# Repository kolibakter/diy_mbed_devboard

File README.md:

# DIY mbed devboard.

This board is for prototyping the mbed HDK for LPC1768 on a board.

[`Link to BOM`](https://docs.google.com/spreadsheets/d/1FSUZfUqJZ9Wz-e41FTdCeESnldcWK53uHcWxY3N1jUs/edit?usp=sharing)

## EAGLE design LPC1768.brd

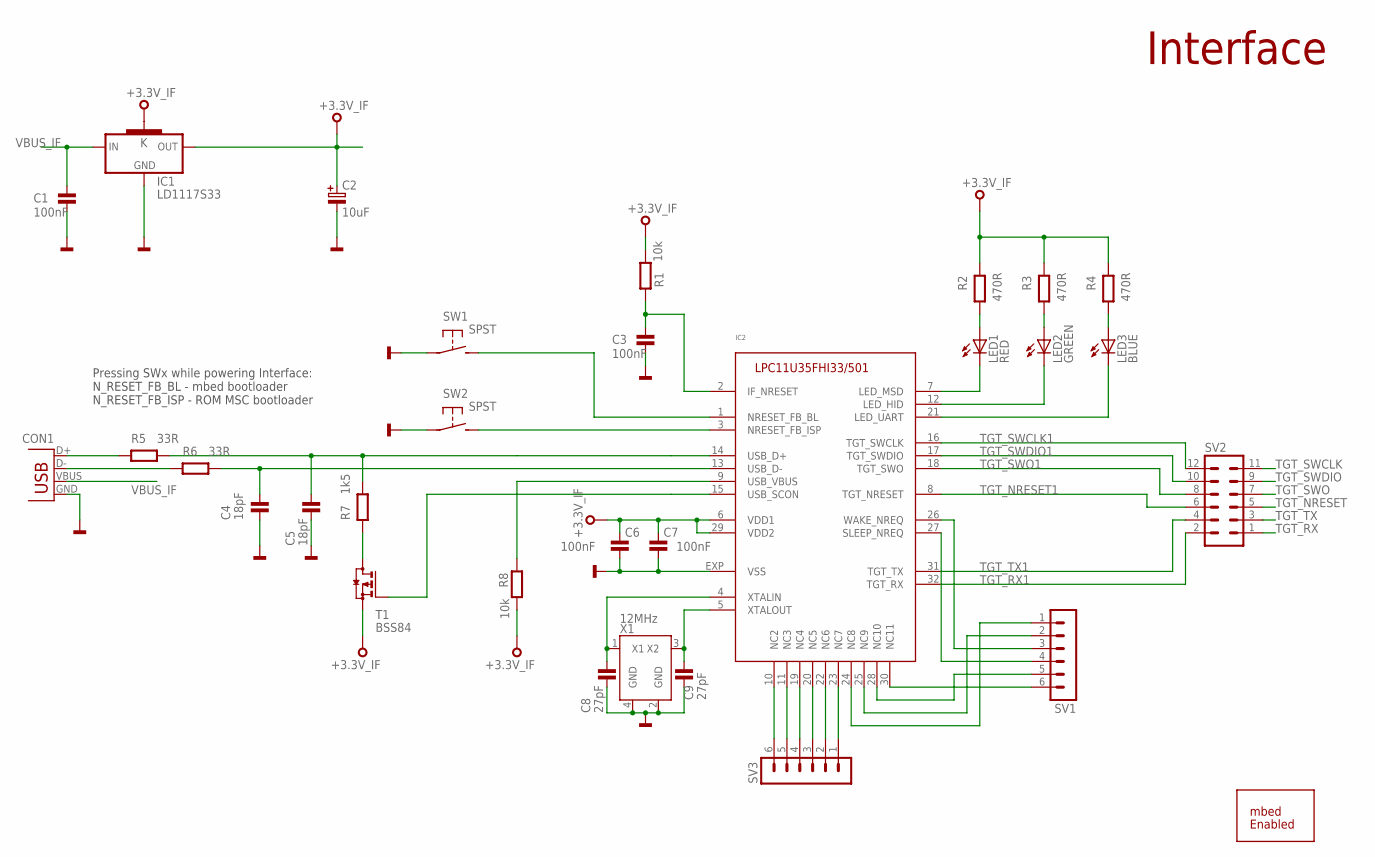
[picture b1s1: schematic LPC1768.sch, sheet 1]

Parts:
C1, C3, C6, C7: 100nF; 0603
C2: 10uF; CASE-B
C4, C5: 18pF; 0603
C8, C9: 27pF; 0603
CON1: USB-MB-S
IC1: LD1117S33; SOT223
IC2: IF-LPC11U35; HVQFN33
LED1: RED; CHIPLED_0603
LED2: GREEN; CHIPLED_0603
LED3: BLUE; CHIPLED_0603
R1, R8: 10k; 0603
R2, R3, R4: 470R; 0603
R5, R6: 33R; 0603
R7: 1k5; 0603
SS1: MBED-ENABLED-LOGOMEDIUM; MBED-ENABLED-LOGO-500X500-MIL
SV1, SV3: MA06-1
SV2: MA06-2
SW1, SW2: SPST; DTSM-32S-B
T1: BSS84; SOT23
X1: 12MHz; OSC_CMD_32_25

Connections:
+3.3V_IF: C2.1, C6.1, C7.1, IC1.2 (OUT), IC1.4 (K), IC2.6 (VDD1), IC2.29 (VDD2), R1.2, R2.1, R3.1, R4.1, R8.2, T1.2 (S)
GND: C1.2, C2.2, C3.2, C4.2, C5.2, C6.2, C7.2, C8.2, C9.2, CON1.GND, IC1.1 (GND), IC2.EXP (VSS), SW1.P$1, SW2.P$1, X1.2 (GND), X1.4 (GND); also elsewhere on the board
GREEN: IC2.12 (LED_HID), LED2.C
GREEN1: IC2.7 (LED_MSD), LED1.C
unnamed: C5.1, IC2.14 (USB_D+), R5.2, R7.2
unnamed: C4.1, IC2.13 (USB_D-), R6.2
unnamed: CON1.D-, R6.1
unnamed: CON1.D+, R5.1
unnamed: C3.1, IC2.2 (IF_NRESET), R1.1
unnamed: R7.1, T1.3 (D)
unnamed: IC2.9 (USB_VBUS), R8.1
unnamed: LED1.A, R2.2
unnamed: LED2.A, R3.2
unnamed: C8.1, IC2.4 (XTALIN), X1.1 (X1)
unnamed: C9.1, IC2.5 (XTALOUT), X1.3 (X2)
unnamed: IC2.21 (LED_UART), LED3.C
unnamed: IC2.1 (NRESET_FB_BL), SW1.P$2 (S)
unnamed: IC2.3 (NRESET_FB_ISP), SW2.P$2 (S)
unnamed: LED3.A, R4.2
unnamed: IC2.15 (USB_SCON), T1.1 (G)
unnamed: IC2.30 (NC11), SV1.6
unnamed: IC2.28 (NC10), SV1.5
unnamed: IC2.27 (SLEEP_NREQ), SV1.4
unnamed: IC2.26 (WAKE_NREQ), SV1.3
unnamed: IC2.25 (NC9), SV1.2
unnamed: IC2.24 (NC8), SV1.1
unnamed: IC2.10 (NC2), SV3.6
unnamed: IC2.11 (NC3), SV3.5
unnamed: IC2.19 (NC4), SV3.4
unnamed: IC2.20 (NC5), SV3.3
unnamed: IC2.22 (NC6), SV3.2
unnamed: IC2.23 (NC7), SV3.1
TGT_NRESET: SV2.5; also elsewhere on the board
TGT_NRESET1: IC2.8 (TGT_NRESET), SV2.6
TGT_RX: SV2.1; also elsewhere on the board
TGT_RX1: IC2.32 (TGT_RX), SV2.2
TGT_SWCLK: SV2.11; also elsewhere on the board
TGT_SWCLK1: IC2.16 (TGT_SWCLK), SV2.12
TGT_SWDIO: SV2.9; also elsewhere on the board
TGT_SWDIO1: IC2.17 (TGT_SWDIO), SV2.10
TGT_SWO: SV2.7; also elsewhere on the board
TGT_SWO1: IC2.18 (TGT_SWO), SV2.8
TGT_TX: SV2.3; also elsewhere on the board
TGT_TX1: IC2.31 (TGT_TX), SV2.4
VBUS_IF: C1.1, CON1.VBUS, IC1.3 (IN); also elsewhere on the board

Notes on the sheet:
Interface
Pressing SWx while powering Interface: N_RESET_FB_BL - mbed bootloader N_RESET_FB_ISP - ROM MSC bootloader

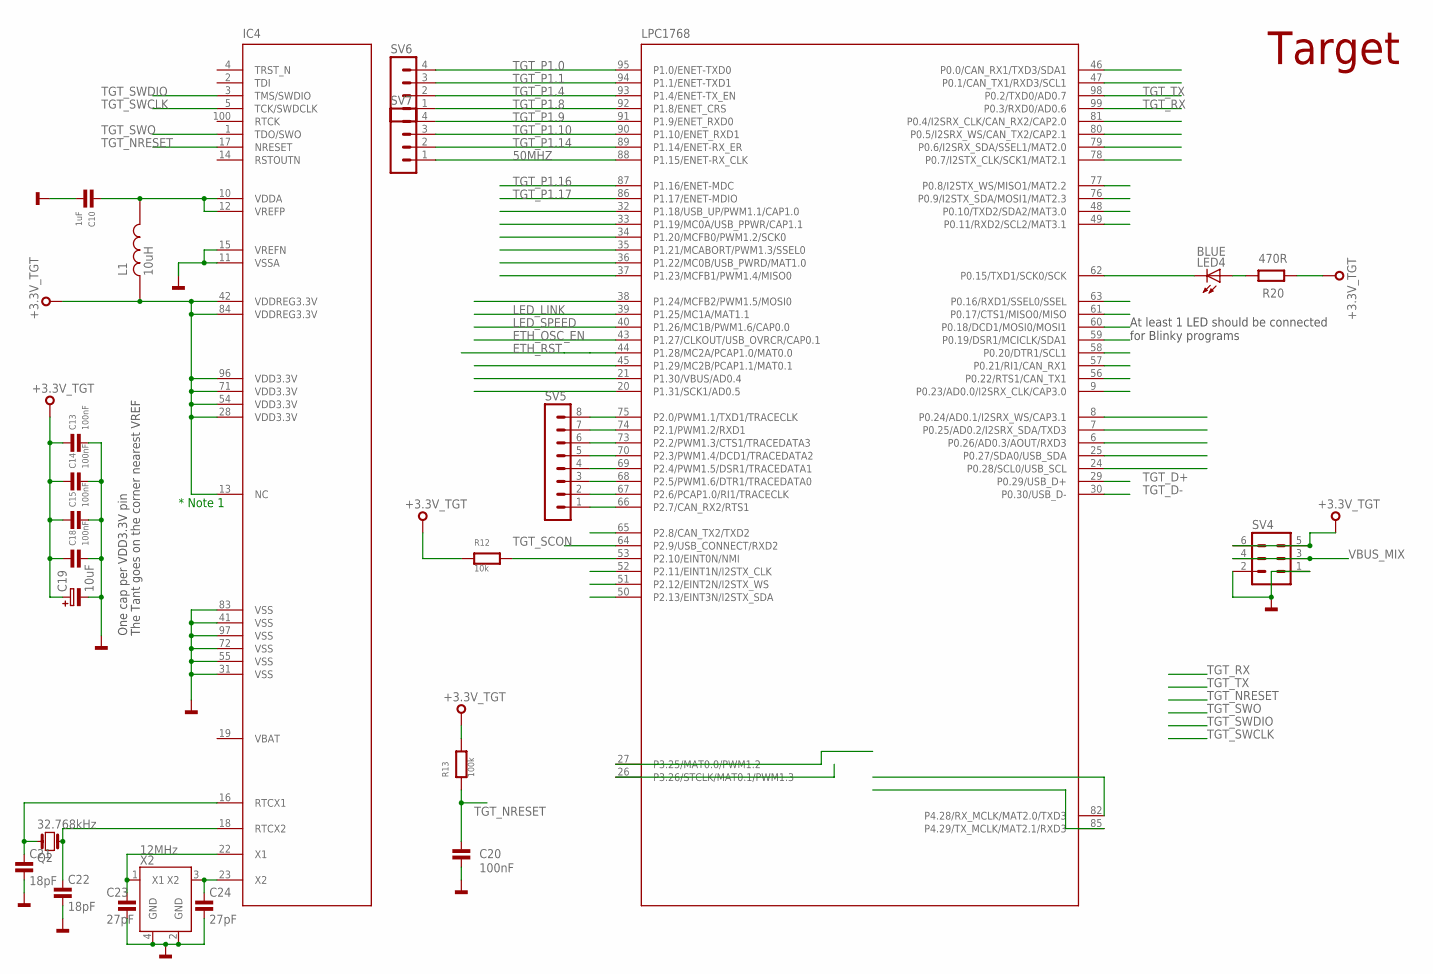
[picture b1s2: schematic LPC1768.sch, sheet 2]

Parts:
C10: 1uF; 0603
C13, C14, C15, C18, C20: 100nF; 0603
C19: 10uF; CASE-B
C21, C22: 18pF; 0603
C23, C24: 27pF; 0603
IC4: LPC1768; LQFP100
L1: 10uH; 0603
LED4: BLUE; CHIPLED_0603
Q2: 32.768kHz; FC135
R12: 10k; 0603
R13: 100k; 0603
R20: 470R; 0603
SV4: MA03-2
SV5: MA08-1
SV6, SV7: MA04-1
X2: 12MHz; OSC_CMD_32_25

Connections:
50MHZ: IC4.88 (P1.15/ENET-RX_CLK), SV7.1
+3.3V_TGT: C13.1, C14.1, C15.1, C18.1, C19.1, IC4.13 (NC), IC4.28 (VDD3.3V), IC4.42 (VDDREG3.3V), IC4.54 (VDD3.3V), IC4.71 (VDD3.3V), IC4.84 (VDDREG3.3V), IC4.96 (VDD3.3V), L1.1, R12.1, R13.2, R20.1, SV4.5, SV4.6; also elsewhere on the board
ETH_OSC_EN: IC4.43 (P1.27/CLKOUT/USB_OVRCR/CAP0.1)
ETH_RST: IC4.44 (P1.28/MC2A/PCAP1.0/MAT0.0)
GND: C10.2, C13.2, C14.2, C15.2, C18.2, C19.2, C20.1, C21.1, C22.1, C23.1, C24.1, IC4.11 (VSSA), IC4.15 (VREFN), IC4.31 (VSS), IC4.41 (VSS), IC4.55 (VSS), IC4.72 (VSS), IC4.83 (VSS), IC4.97 (VSS), SV4.1, SV4.2, X2.2 (GND), X2.4 (GND); also elsewhere on the board
LED_LINK: IC4.39 (P1.25/MC1A/MAT1.1)
LED_SPEED: IC4.40 (P1.26/MC1B/PWM1.6/CAP0.0)
unnamed: C10.1, IC4.10 (VDDA), IC4.12 (VREFP), L1.2
unnamed: IC4.53 (P2.10/EINT0N/NMI), R12.2
unnamed: C23.2, IC4.22 (X1), X2.1 (X1)
unnamed: C21.2, IC4.16 (RTCX1), Q2.X2 (2)
unnamed: C22.2, IC4.18 (RTCX2), Q2.X1 (1)
unnamed: IC4.62 (P0.15/TXD1/SCK0/SCK), LED4.C
unnamed: LED4.A, R20.2
unnamed: IC4.75 (P2.0/PWM1.1/TXD1/TRACECLK), SV5.8
unnamed: IC4.74 (P2.1/PWM1.2/RXD1), SV5.7
unnamed: IC4.73 (P2.2/PWM1.3/CTS1/TRACEDATA3), SV5.6
unnamed: IC4.70 (P2.3/PWM1.4/DCD1/TRACEDATA2), SV5.5
unnamed: IC4.69 (P2.4/PWM1.5/DSR1/TRACEDATA1), SV5.4
unnamed: IC4.68 (P2.5/PWM1.6/DTR1/TRACEDATA0), SV5.3
unnamed: IC4.67 (P2.6/PCAP1.0/RI1/TRACECLK), SV5.2
unnamed: IC4.66 (P2.7/CAN_RX2/RTS1), SV5.1
unnamed: C24.2, IC4.23 (X2), X2.3 (X2)
TGT_D+: IC4.29 (P0.29/USB_D+); also elsewhere on the board
TGT_D-: IC4.30 (P0.30/USB_D-); also elsewhere on the board
TGT_NRESET: C20.2, IC4.17 (NRESET), R13.1; also elsewhere on the board
TGT_P1.0: IC4.95 (P1.0/ENET-TXD0), SV6.4
TGT_P1.1: IC4.94 (P1.1/ENET-TXD1), SV6.3
TGT_P1.4: IC4.93 (P1.4/ENET-TX_EN), SV6.2
TGT_P1.8: IC4.92 (P1.8/ENET_CRS), SV6.1
TGT_P1.9: IC4.91 (P1.9/ENET_RXD0), SV7.4
TGT_P1.10: IC4.90 (P1.10/ENET_RXD1), SV7.3
TGT_P1.14: IC4.89 (P1.14/ENET-RX_ER), SV7.2
TGT_P1.16: IC4.87 (P1.16/ENET-MDC)
TGT_P1.17: IC4.86 (P1.17/ENET-MDIO)
TGT_RX: IC4.99 (P0.3/RXD0/AD0.6); also elsewhere on the board
TGT_SCON: IC4.64 (P2.9/USB_CONNECT/RXD2); also elsewhere on the board
TGT_SWCLK: IC4.5 (TCK/SWDCLK); also elsewhere on the board
TGT_SWDIO: IC4.3 (TMS/SWDIO); also elsewhere on the board
TGT_SWO: IC4.1 (TDO/SWO); also elsewhere on the board
TGT_TX: IC4.98 (P0.2/TXD0/AD0.7); also elsewhere on the board
VBUS_MIX: SV4.3, SV4.4; also elsewhere on the board

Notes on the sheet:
The Tant goes on the corner nearest VREF
One cap per VDD3.3V pin
* Note 1
Target
At least 1 LED should be connected for Blinky programs

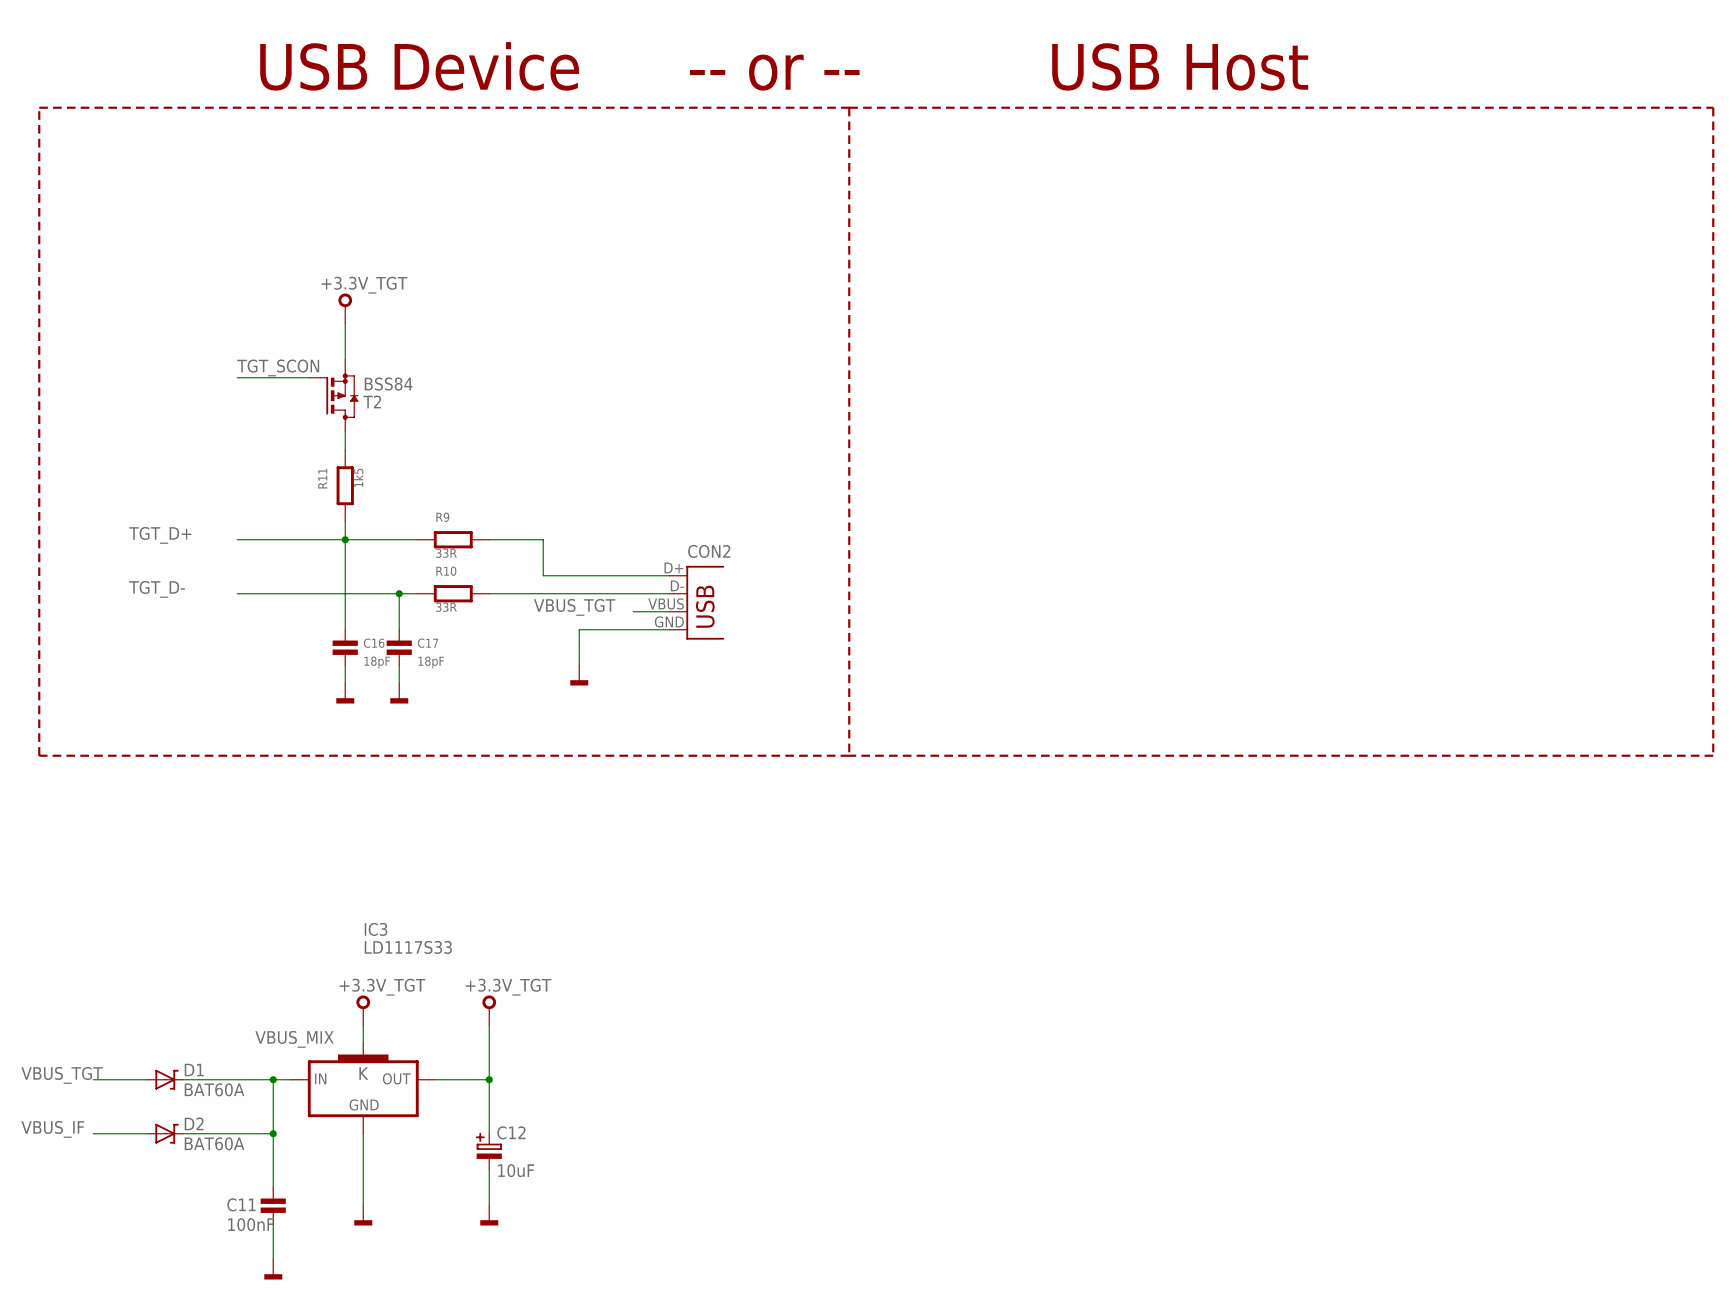
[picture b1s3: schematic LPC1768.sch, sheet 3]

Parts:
C11: 100nF; 0603
C12: 10uF; CASE-B
C16, C17: 18pF; 0603
CON2: USB-MB-S
D1, D2: BAT60A
IC3: LD1117S33; SOT223
R9, R10: 33R; 0603
R11: 1k5; 0603
T2: BSS84; SOT23

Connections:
+3.3V_TGT: C12.1, IC3.2 (OUT), IC3.4 (K), T2.2 (S); also elsewhere on the board
GND: C11.2, C12.2, C16.2, C17.2, CON2.GND, IC3.1 (GND); also elsewhere on the board
unnamed: R11.1, T2.3 (D)
unnamed: CON2.D-, R10.2
unnamed: CON2.D+, R9.2
TGT_D+: C16.1, R9.1, R11.2; also elsewhere on the board
TGT_D-: C17.1, R10.1; also elsewhere on the board
TGT_SCON: T2.1 (G); also elsewhere on the board
VBUS_IF: D2.A; also elsewhere on the board
VBUS_MIX: C11.1, D1.K, D2.K, IC3.3 (IN); also elsewhere on the board
VBUS_TGT: CON2.VBUS, D1.A

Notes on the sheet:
USB Device
USB Host
-- or --

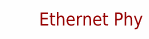
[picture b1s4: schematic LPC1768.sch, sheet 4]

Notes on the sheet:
Ethernet Phy

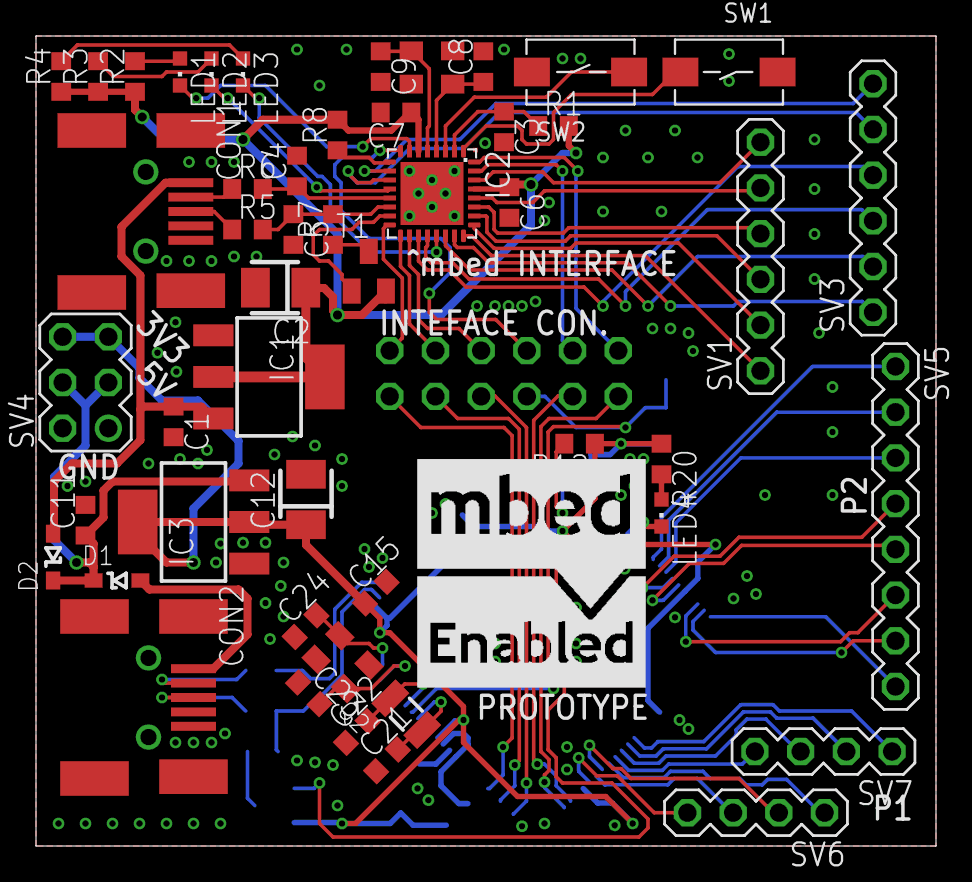
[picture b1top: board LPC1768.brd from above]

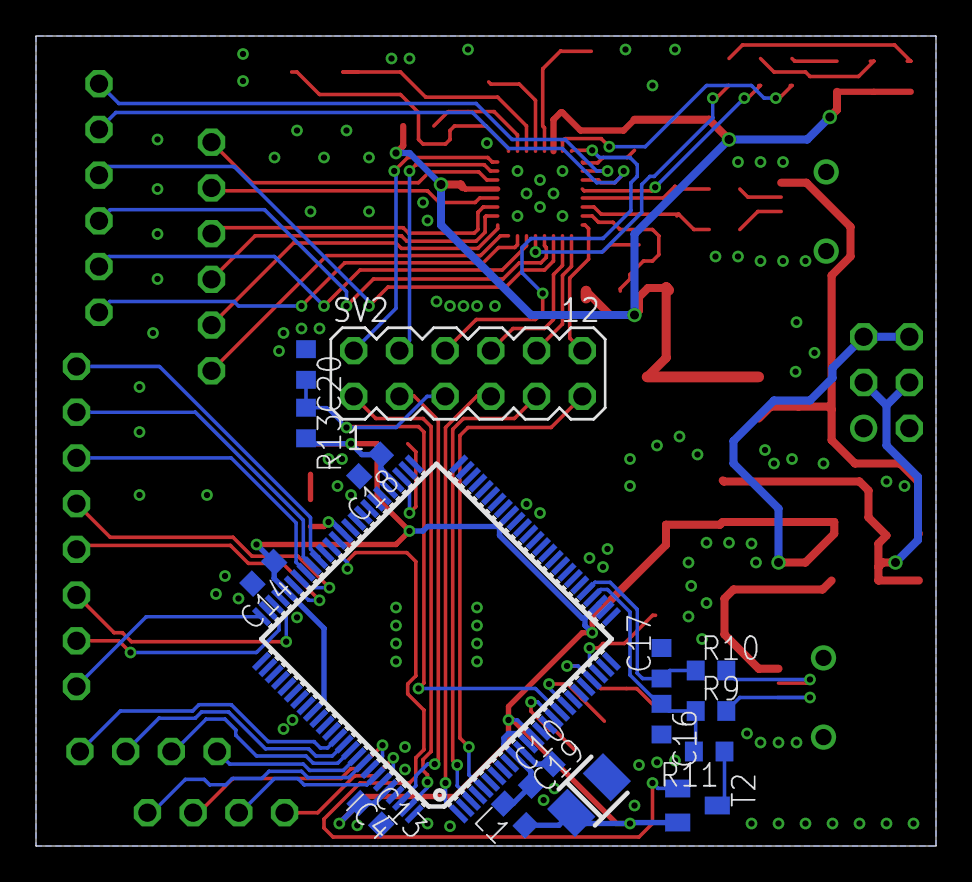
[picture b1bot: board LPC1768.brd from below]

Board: 2 copper layers, 50.0 x 45.0 mm, 66 parts (16 on the bottom side), 78 nets.

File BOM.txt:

Partlist exported from D:/git/diy_mbed_devboard/LPC1768.sch at 03.06.2016 17:00

Qty Value                   Device                  Package                       Parts                                        Description                
1                           IF-LPC11U35             HVQFN33                       IC2                                                                     
1                           MA03-2                  MA03-2                        SV4                                          PIN HEADER                 
2                           MA04-1                  MA04-1                        SV6, SV7                                     PIN HEADER                 
2                           MA06-1                  MA06-1                        SV1, SV3                                     PIN HEADER                 
1                           MA06-2                  MA06-2                        SV2                                          PIN HEADER                 
1                           MA08-1                  MA08-1                        SV5                                          PIN HEADER                 
1   100k                    R0603                   0603                          R13                                                                     
10  100nF                   C0603                   0603                          C1, C3, C6, C7, C11, C13, C14, C15, C18, C20                            
3   10k                     R0603                   0603                          R1, R8, R12                                                             
3   10uF                    C-POLB                  CASE-B                        C2, C12, C19                                                            
1   10uH                    L                       0603                          L1                                                                      
2   12MHz                   ABM8                    OSC_CMD_32_25                 X1, X2                                                                  
6   18pF                    C0603                   0603                          C4, C5, C16, C17, C21, C22                                              
2   1k5                     R0603                   0603                          R7, R11                                                                 
1   1uF                     C0603                   0603                          C10                                                                     
4   27pF                    C0603                   0603                          C8, C9, C23, C24                                                        
1   32.768kHz               Q_FC135                 FC135                         Q2                                                                      
4   33R                     R0603                   0603                          R5, R6, R9, R10                                                         
4   470R                    R0603                   0603                          R2, R3, R4, R20                                                         
2   BAT60A                  BAT60A                  BAT60A                        D1, D2                                                                  
2   BLUE                    LED0603                 CHIPLED_0603                  LED3, LED4                                                              
2   BSS84                   BSS84                   SOT23                         T1, T2                                       P-CHANNEL MOS FET          
1   GREEN                   LED0603                 CHIPLED_0603                  LED2                                                                    
2   LD1117S33               LD1117S33               SOT223                        IC1, IC3                                     VOLTAGE REGULATOR SMD 3,3V 
1   LPC1768                 LPC1768                 LQFP100                       IC4                                                                     
1   MBED-ENABLED-LOGOMEDIUM MBED-ENABLED-LOGOMEDIUM MBED-ENABLED-LOGO-500X500-MIL SS1                                                                     
1   RED                     LED0603                 CHIPLED_0603                  LED1                                                                    
2   SPST                    SPST                    DTSM-32S-B                    SW1, SW2                                                                
2   USB-MB-S                USB-MB-S                USB-MB-S                      CON1, CON2                                   USB Connectors

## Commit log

2016-06-01 Added mbed HDK files.
2016-06-06 Added mbed HDK library. Modified schematic and added board. Added BOM. Added some drc files.
2016-06-06 Updated readme.
2016-06-06 Readme update.
2016-06-06 Small changes for manufacturing. Added gerber files.
2016-06-06 Updated readme. Added gerber zip.
2016-06-06 Update readme.
